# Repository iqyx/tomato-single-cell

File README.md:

A single cell Li-Ion/Li-Po/LiFePO4 MPPT solar charger
===========================================================

Roadmap for the 1.0.0 firmware
-------------------------------------

- fw: enable setting of the solar panel MPP voltage
- fw: enable setting of the battery float voltage (3.6V/4.2V)
- fw: enable setting of the battery UVLO
- fw: save the settings in a nonvolatile storage
- fw: locking/unlocking settings which may cause damage (battery voltages, etc.)

Firmware changelog (1.0.0-dev)
-------------------------------------

- fw: added I2C timeouts to fix communication errors with the STC3100 battery gauge/monitor
- fw: interface was changed to protocol buffers (using the nanopb library) and defined as a proto file
- fw: firmware has been split into multiple files
- fw: added IWDG watchdog
- fw: added undervoltage shutdown for the Vbus converter (hardcoded now)
- fw: added NTC battery temperature reading

TODO
------------

- fw: add periodic scan of the Vin_reg to fnd an optimal MPP voltage
- fw: add perturb and observe algo for setting of the MPP voltage
- fw: add status led
- fw: add stop mode when not charging (PWM is off)

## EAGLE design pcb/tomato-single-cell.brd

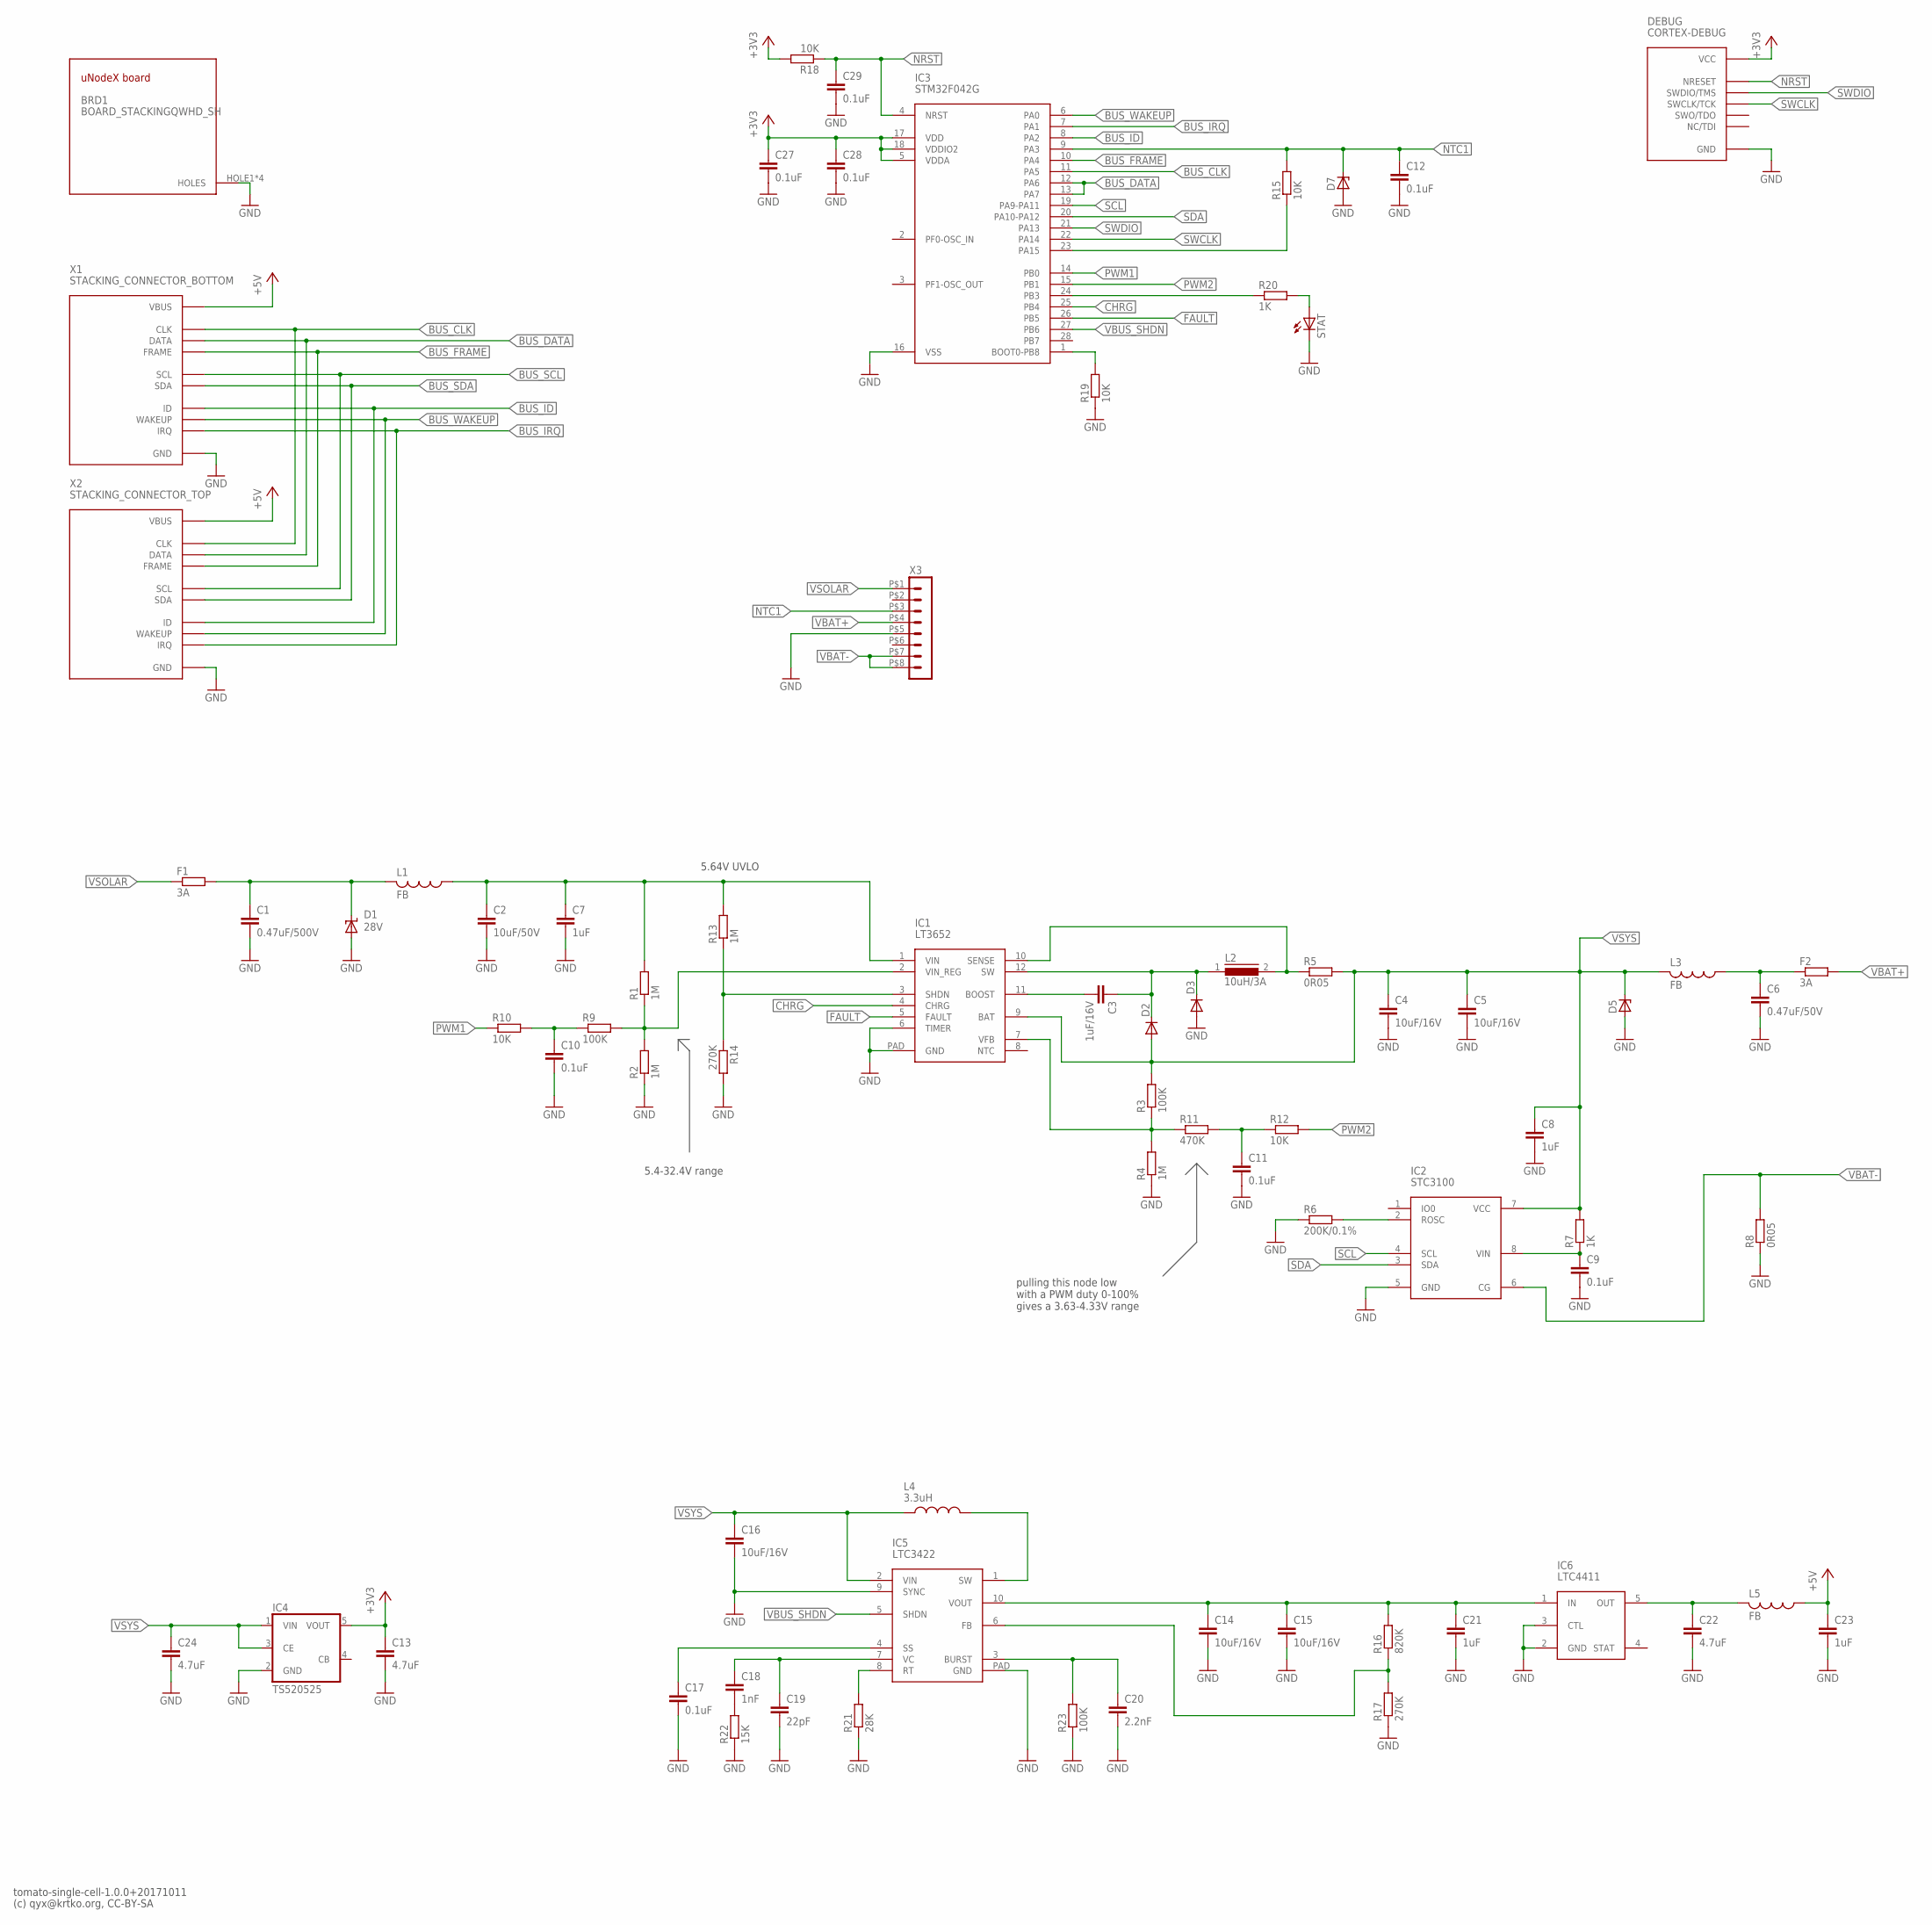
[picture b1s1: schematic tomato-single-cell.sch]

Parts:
BRD1: BOARD_STACKINGQWHD_SH; QWHD_SHARP_CORNERS
C1: 0.47uF/500V; C1206
C2: 10uF/50V; C2220K
C3: 1uF/16V; C0805
C4, C5, C14, C15, C16: 10uF/16V; C1206
C6: 0.47uF/50V; C0805
C7, C21, C23: 1uF; C0805
C8: 1uF; C0603
C9, C10, C11, C12, C17, C27, C28, C29: 0.1uF; C0603
C13, C22, C24: 4.7uF; C0805
C18: 1nF; C0603
C19: 22pF; C0603
C20: 2.2nF; C0603
D1: 28V; SMBJ
D2, D3: DIODE-SOD323-W; SOD323-W
D5, D7: ZENER-DIODESOT23; SOT23
DEBUG: CORTEX-DEBUG
F1, F2: 3A; R1206
IC1: LT3652; MSOP12-PAD
IC2: STC3100; MSOP8
IC3: STM32F042G; UFQFPN28
IC4: TS520525; SOT25
IC5: LTC3422; DFN10-3X3
IC6: LTC4411; SOT23-5
L1, L3, L5: FB; L3216C
L2: 10uH/3A; DR74
L4: 3.3uH; XAL50XX
R1, R2, R4, R13: 1M; R0603
R3, R9, R23: 100K; R0603
R5, R8: 0R05; R1206
R6: 200K/0.1%; R0603
R7, R20: 1K; R0603
R10, R12, R15, R18, R19: 10K; R0603
R11: 470K; R0603
R14, R17: 270K; R0603
R16: 820K; R0603
R21: 28K; R0603
R22: 15K; R0603
STAT: LEDCHIPLED_0805; CHIPLED_0805
X1: STACKING_CONNECTOR_BOTTOM; HAR-FLEX-BOTTOM-12P
X2: STACKING_CONNECTOR_TOP; HAR-FLEX-TOP-12P
X3: HEADER_POS8_43045-0800; 43045-0800

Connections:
+3V3: C13.1, C27.1, C28.1, DEBUG.VCC, IC3.5 (VDDA), IC3.17 (VDD), IC3.18 (VDDIO2), IC4.5 (VOUT), R18.2
+5V: C23.1, L5.1, X1.VBUS, X2.VBUS
BUS_CLK: IC3.11 (PA5), X1.CLK, X2.CLK
BUS_DATA: IC3.12 (PA6), IC3.13 (PA7), X1.DATA, X2.DATA
BUS_FRAME: IC3.10 (PA4), X1.FRAME, X2.FRAME
BUS_ID: IC3.8 (PA2), X1.ID, X2.ID
BUS_IRQ: IC3.7 (PA1), X1.IRQ, X2.IRQ
BUS_SCL: X1.SCL, X2.SCL
BUS_SDA: X1.SDA, X2.SDA
BUS_WAKEUP: IC3.6 (PA0), X1.WAKEUP, X2.WAKEUP
CHRG: IC1.4 (CHRG), IC3.25 (PB4)
FAULT: IC1.5 (FAULT), IC3.26 (PB5)
GND: BRD1.HOLE1, BRD1.HOLE2, BRD1.HOLE3, BRD1.HOLE4, C1.2, C2.2, C4.2, C5.2, C6.2, C7.2, C8.2, C9.2, C10.2, C11.2, C12.2, C13.2, C14.2, C15.2, C16.2, C17.2, C19.2, C20.2, C21.2, C22.2, C23.2, C24.2, C27.2, C28.2, C29.2, D1.A, D3.A, D5.1 (A), D7.1 (A), DEBUG.GND1 (GND), DEBUG.GND2 (GND), DEBUG.GND_DETECT (GND), IC1.6 (TIMER), IC1.PAD (GND), IC2.5 (GND), IC3.16 (VSS), IC4.2 (GND), IC5.9 (SYNC), IC5.PAD (GND), IC6.2 (GND), IC6.3 (CTL), R2.1, R4.1, R6.1, R8.1, R14.2, R17.1, R19.1, R21.1, R22.1, R23.1, STAT.C, X1.GND1 (GND), X1.GND2 (GND), X1.GND3 (GND), X1.H1 (GND), X1.H2 (GND), X1.H3 (GND), X1.H4 (GND), X2.GND1 (GND), X2.GND2 (GND), X2.GND3 (GND), X2.H1 (GND), X2.H2 (GND), X2.H3 (GND), X2.H4 (GND), X3.P$5 (5)
unnamed: C1.1, D1.C, F1.2, L1.2
unnamed: IC2.2 (ROSC), R6.2
unnamed: IC1.2 (VIN_REG), R1.1, R2.2, R9.2
unnamed: C9.1, IC2.8 (VIN), R7.1
unnamed: C10.1, R9.1, R10.2
unnamed: C11.1, R11.2, R12.1
unnamed: IC1.3 (SHDN), R13.1, R14.1
unnamed: C3.1, D2.C, D3.C, IC1.12 (SW), L2.1
unnamed: C17.1, IC5.4 (SS)
unnamed: C3.2, IC1.11 (BOOST)
unnamed: IC1.10 (SENSE), L2.2, R5.1
unnamed: IC1.7 (VFB), R3.1, R4.2, R11.1
unnamed: IC3.23 (PA15), R15.1
unnamed: IC3.24 (PB3), R20.1
unnamed: IC5.1 (SW), L4.2
unnamed: C14.1, C15.1, C21.1, IC5.10 (VOUT), IC6.1 (IN), R16.2
unnamed: IC5.6 (FB), R16.1, R17.2
unnamed: IC5.8 (RT), R21.2
unnamed: C18.2, R22.2
unnamed: C18.1, C19.1, IC5.7 (VC)
unnamed: C20.1, IC5.3 (BURST), R23.2
unnamed: C22.1, IC6.5 (OUT), L5.2
unnamed: IC3.1 (BOOT0-PB8), R19.2
unnamed: R20.2, STAT.A
NRST: C29.1, DEBUG.NRESET, IC3.4 (NRST), R18.1
NTC1: C12.1, D7.3 (C), IC3.9 (PA3), R15.2, X3.P$3 (3)
PWM1: IC3.14 (PB0), R10.1
PWM2: IC3.15 (PB1), R12.2
SCL: IC2.4 (SCL), IC3.19 (PA9-PA11)
SDA: IC2.3 (SDA), IC3.20 (PA10-PA12)
SWCLK: DEBUG.SWCLK/TCK, IC3.22 (PA14)
SWDIO: DEBUG.SWDIO/TMS, IC3.21 (PA13)
VBAT+: F2.2, X3.P$4 (4)
VBAT+PO: C6.1, F2.1, L3.1
VBAT-: IC2.6 (CG), R8.2, X3.P$7 (7), X3.P$8 (8)
VBUS_SHDN: IC3.27 (PB6), IC5.5 (SHDN)
VIN: C2.1, C7.1, IC1.1 (VIN), L1.1, R1.2, R13.2
VSOLAR: F1.1, X3.P$1 (1)
VSYS: C4.1, C5.1, C8.1, C16.1, C24.1, D2.A, D5.3 (C), IC1.9 (BAT), IC2.7 (VCC), IC4.1 (VIN), IC4.3 (CE), IC5.2 (VIN), L3.2, L4.1, R3.2, R5.2, R7.2

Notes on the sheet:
tomato-single-cell-1.0.0+20171011
(c) qyx@krtko.org, CC-BY-SA
pulling this node low with a PWM duty 0-100% gives a 3.63-4.33V range
5.4-32.4V range
5.64V UVLO

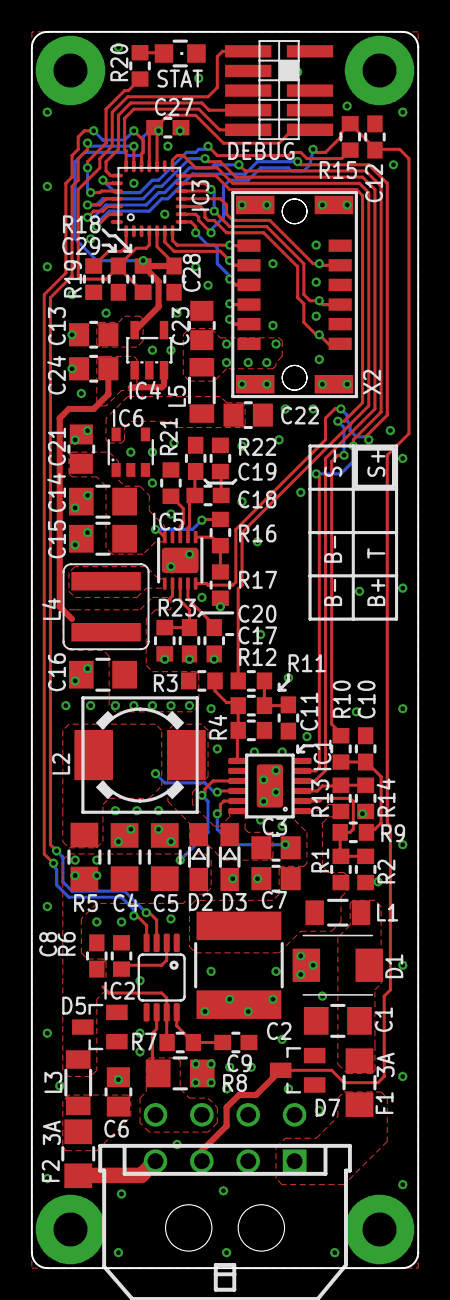
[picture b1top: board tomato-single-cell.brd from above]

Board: 2 copper layers, 25.0 x 80.0 mm, 74 parts (0 on the bottom side), 52 nets.

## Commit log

2017-11-01 Add .gitignore file to ignore temporary and compiled files
2017-11-06 Add a basic PoC firmware
    The firmware supports communication over the UXB bus and
    reading the STC3100 battery gauge/monitor registers to
    measure battery voltage, charging/discharging current,
    chip temperature and cumulated battery charge. Those values
    are exported over the bus in a simple way (no protobufs yet).
2017-11-06 Add schematic diagram and a board layout
2017-11-06 Add Gerber exports (ready for seeedstudio)
2017-11-06 Add README file with a to-do list
2017-11-09 Add nanopb library submodule
2017-11-09 Split fw into multiple files and use protocol buffers to communicate
2017-11-09 Enable the IWDG watchdog
2017-11-10 Add battery NTC temperature reading and an UVLO function
2017-11-13 Add UVLO hysteresis
2017-11-13 Run the MCU at 1MHz, switch to 8MHz on uxb request
2017-11-13 Fix uxb bus delay
2017-12-15 Update libuxb library and adjust the code
2017-12-15 Quick fix battery type to 1cell Li-Ion & add value watchdog
